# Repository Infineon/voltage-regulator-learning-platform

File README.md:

# Learning Platform for Switching Regulators

This platform is designed with the intention of providing an interactive educational opertunity to university students with diverse technical backgrounds on switching regulators (namely buck converters). The project aims to develop the students' skills on using basic microcontroller IO features as starters and then build upon those skills to use a gate driver to implement a buck converter and monitor its output and efficiency. Along the Buck converter design process, the students get to use the the on board's peripherals to understand the different properties of buck converters and how they could be optimized. 

## Project's History
The project was introduced as a bachelor thesis of **Lukas Wiegert**. (*version 1.0*). Continued and further developed by **Adrian Keil** (*Versions: 1.0 ,1.1 ,1.2*) and finalized by **Youssef Tarkhan** (*versions: 2.0, 2.1*). The latest update was done 2025 from **David Lopez** (*version: PCBv3*). The boards are used by the Technical University of Munich to teach the students and assess the quality and functionality of these boards and provide an open source curriculum.

# Latest Update PCBv3

The latest update included mainly following changes:
- Removing the 3.3V rail. Only two remaining power supply rails (12V for power part, 5V for digital logik and measurements).
- Fixed common error that current measurement opamps burn because of shorted ouputs (male pinheaders get easily shorted when probed)
- Additional output resistance as second safety measure

# Board Breakdown

**Brief summary**: As you can see from the block diagram, the board needs an input connection. (Bannana ports are provided at the bottom side of the board).  After the board makes sure that the polarity and the voltage are in check, the power is fed into the board's internal powersupply compartment. If the voltage level is below 10V then you will observe the undervoltage LED glowing in RED. The powerline feeding the whole board interfaces two optional possibilities for input current measurement. Power is then fed onto the power stage which consists of the components needed for the buck switching with a **VOut** output (*In older versions of the board there used to be additional banana ports for the **Vout** terminal and an additional ground banana port*.) Power is additionally fed into the arduino peripherals for basic microcontroller usage (LEDS, Switches, Buttons and Potentiometers). 

*Note that for every measurable quantity such as the input current for instance, there is a testpoint that could be attached onto an oscilloscope in order to have an easier experience when trying the measure this quantity*

# Microcontroller Pinouts
This platform is an arduino compatable shield. It is intended to be used in combination with the XMC1100 Bootkit
The labelling of the XMC1100 Bootkit pins is placed on the bottom layer's silk screen.

>An Arduino compatible shield is a hardware expansion board that is designed to be compatible with Arduino microcontroller boards. It is called a "shield" because it typically attaches on top of an Arduino board, extending its capabilities and providing additional functionalities

<center>

## XMC 1100 Bootkit Pins
| Pin   | Net                   | Type   | Description                                |
|-------|-----------------------|--------|--------------------------------------------|
| A0    | In_Curr_ADC           | Input  | Analog input for current measurement        |
| A1    | Inductor_Current_ADC  | Input  | Analog input for inductor current sensing   |
| A2    | UserPot1              | Input  | Analog input for user potentiometer 1       |
| A3    | Vin_Meas              | Input  | Analog input for voltage measurement        |
| A4    | Vout_Meas             | Input  | Analog input for output voltage measurement |
| A5    | NTC_ext               | Input  | Analog input for external NTC temperature    |
| D0    | NC                    | NC     | Not connected                              |
| D1    | NC                    | NC     | Not connected                              |
| D2    | UserBtn1              | Input  | Digital input for user button 1             |
| D3    | Cntrl1                | Output | Digital output for control signal 1         |
| D4    | Cntrl2                | Output | Digital output for control signal 2         |
| D5    | Cntrl3                | Output | Digital output for control signal 3         |
| D6    | Buck_Cntrl_Arduino    | Output | Digital output for Arduino buck control     |
| D7    | UserBtn2              | Input  | Digital input for user button 2             |
| D8    | Shutdown              | Input  | Digital input for shutdown signal           |
| D9    | User_LED1             | Output | Digital output for user LED 1               |
| D10   | User_LED2             | Output | Digital output for user LED 2               |
| D11   | User_LED3             | Output | Digital output for user LED 3               |
| D12   | UserSw                | Input  | Digital input for user switch               |
| D13   | User_LED4             | Output | Digital output for user LED 4               |

<br><br>
</center>

> **Note:** The following code snippet defines all the required arduino pins for using the platform, simply copy it to the beginning of your code (before the setup)

<br><br>
<center>

```cpp
// Define all Arduino pins
// Digital Out
#define USER_LED1     9
#define USER_LED2     10
#define USER_LED3     11
#define USER_LED4     13
#define BUCK_PIN      6

// Digital In
#define USER_BTN1     2
#define USER_BTN2     7
#define SHUTDOWN      8
#define USER_SW       12

// Analog In
#define IN_CURR       A0
#define INDUCTOR_CURR A1
#define USER_POTI     A2

#define VIN_MEAS      A3
#define VOUT_MEAS     A4
#define NTC           A5

```

</center>
<br>
<br>
Also add the following pin setup lines into your setup loop 

<center>

```cpp
  pinMode(BUCK_PIN, OUTPUT);
  pinMode(USER_LED1, OUTPUT);
  pinMode(USER_LED2, OUTPUT);
  pinMode(USER_LED3, OUTPUT);
  pinMode(USER_LED4, OUTPUT);
  pinMode(USER_BTN1, INPUT);
  pinMode(USER_BTN2, INPUT);
  pinMode(USER_SW, INPUT);
  pinMode(SHUTDOWN,INPUT);
  pinMode(USER_POTI,INPUT);
  pinMode(INDUCTOR_CURR,INPUT);
  pinMode(IN_CURR,INPUT);

```

</center>
<br>
<br>

> **Note:** In order to use both user buttons you'll have to unsolder the resistor at Pin 1.4 (check out the diagram below)

<p align="center">
  
</p>

# Power Input
The board is equipped with a variety of safety measures to ensure that it not only has a long life, but also ensure that students get to have a higher level of freedom with it. The board is to be powered with a DC power supply through banana plugs. 

- First stage of the power input is going through the reverse polarity protection circuit, following by over voltage detection circuit. ( In case of an overvoltage detection, power is cut from the main circuit through a MOSFET) Note that the board supports up to 30V but has a recommended to be used in the 15V input range
- Voltage is then delivered to the board compartments : Powersupply, Safety Comparator, Powerstage stage & Miscellaneous  

# Power Supply
The Optimum input Voltage for the board input is around **15V**. In case the voltage goes over 19V the board goes into a hysterisis where it only gets back in operation when the voltage level goes below ****. Feel free to check the simulation files if you want to get a deeper insight into how the hysterisis works on a circuit design level. (You will have to install the spice model files for the ATL431, [click here](https://www.youtube.com/watch?v=EwAxUvS5z-0) for a guide on how to do that)
Along with the input being fed into the board, the board additionally has 3 additional power components which are:
<center>

 **12V LDO**: 
<p align="center">
  
</p>
	- Gate driver IC
	- Input Internal Current Sense Amplifier
	- Safety Latch 
	- Safety Circuit Comparator
	- Safety LEDs

**5V Buck**: 
<p align="center">
  
</p>
	- 3V3 LDO
	- Arduino Compatable MCU 
	- Safety Circuitry Voltage Threshhold (*Under-Voltage Detection*)
  
**3V3 LDO**:
<p align="center">
  
</p>
	- Output Internal Current Sense Amplifier
	- ADC Compensation for MCU Input
	- Safety Comparator Circuit
</center>		

<br><br>

# Safety
The safety compartment of the board is comprised mainly of a comparator and a safety latch, where when the safety comparator detects a flag, this flag is saved on the latch. (To reset the latch all you'll have to do is press the latch reset button)

For example if the undervoltage flag is raised (Input voltage goes below 10V), the undervoltage flag will be raised and the corresponding LED will turn on. Aslong as the latch has not been reset, even if the input voltage goes above 10V, the LED will stay on and the shutdown signal will keep getting sent to the microcontroller and the power components. 

**Flags**

When safety flags are triggered, a **shutdown** signal is generated and the corresponding flag's LED is lit. The **shutdown** signal is delivered to the microcontroller and the power stage components. The powerstage is disabled as long as the shutdown signal is being delivered to its components.  

- **Overcurrent**
  - The output current from the powerstage is measured over a shuntresistor and a current sense amplifier. The output signal is then fed into a the safety comparator, which is compared to a constant reference voltage. (This reference voltage is equal to the corresponding output of the amplifier when the output current is around **2.8A**). 

- **Undervoltage**
  - the input voltage is fed through the two equal value resistors R510 and R511 and the signal is halfed (voltage divider Law), and is then fed into the comparator. As reference the 5V Buck output is fed into the other input of the comparator. If the input voltage goes below 10V , then half of that signal will be lower than 5V and so the undervoltage flag would be triggered.

- **Overtemperature (External)**
  - An NTC is connected on the external resistor board. (Negative Thermal cooefficient resistor; pretty much a fancy word for a resistor, who's resistance value changes when its temperature changes). The NTC's signal is connected to an input of the safety comparator with a reference signal connected to the other input.
    
- **Overtemperature (Internal)**
  - Similar to external overtemperature detection, however the NTC is onboard and there is a variable resisotr on board to calibrate the onboard overtemperature limit of the board. 

- **Safety Flag LEDs**
  - you can find the safety LEDs are placed on the top right corner of the PCB

<br><br>
## Miscellaneous
The board is equipped with:
- 1 User programmable potentiometer
  
- 2 User programmable buttons
  
- 4 User programmable LEDs

- 1 User programmable Switch

<br>

##  Buck Operation
The buck operation takes place over a gate driver; what happens: is that the gate driver takes in pulse width modulated signals from the microcontroller (**XMC 1100 Bootkit**) or an external controller through the **PWM** pin on the external control pin header.  The users have to modify the **BUCK CNTRL** switch to adapt the circuitry to whether or not the control signal would be coming from the external control pin header or through the onboard controller pins. The students get to change the frequency and duty cycle of the signal in order to achieve their desired output voltage. 

There are also some jumpers on board that could adjust the output circuity of the buck operation.
Jumpers are available for: 
- Connecting three 10 uF Capacitors 
- Connecting a 220uF capacitor
- Connecting a 15uH inductor

## External Control

Aside from using the board as a shield, it could also just be connected to an external controller circuit.

As shown in the diagram above, using jumper cables, the user externally has access to: 

- Input voltage to through the Banana cables
- 12V Output of the LDO
- 5V Output of the Buck Controller
- 3.3V Output of the LDO
- Input Current Sensor Reading
- Output Current Sensor Reading
- Output Voltage 
- Output Voltage (Calibrated to 0 to 5V)
- External Buck Control
- User Button 1 Input
- User Button 2 Input
- User Switch Input
- User LEDs (1 to 3)
- User Potentiometer 1 Input

### NTC Calibration
- For making sure that the temperature on board is in check, negative thermal coefficient resistors are chosen . The onboard maximum temperature could easily be calibrated by adjusting a potentiometer for temperature limitation between (50°C and 90°C)

## Current Measurement
The main method of current measurement is the combination of a shunt resistor and a current sense amplifier. This setup is repeated in the input and output current measurement system. The operation relies on a voltage drop accross the shunt resistor proportional to the current flowing through it. This voltage drop is amplified by the current sense amplifier into a new voltage value. This voltage value is read by the micro-controller's ADC and it's used to subsequently calculate the value of the current.

the main component (TSC2010IST) in the diagram above is a current sense amplifier. This current sense amplifier is connected over a shunt resistor (pins: 1 & 8). The output of this amplifier is proportional to the amount of current going through the shunt resistor. 

<br>

# Testpoints

The board is equiped with test points to make it easier for students to observe different quantities using an oscilloscope.

<center>

All black testpoints are Ground testpoints

Red testpoints are labelled with their corresponding measurement quantity. 

</center>
<br>

# Simulation Files
To provide a rich experience to students, the simulation files for most of the building blocks of the learning platform are provided. These simulations are accessable on LTSPICE, which is an open source freeware, that is very popular in the industry.  

You can find these simulations under the Directory /Simulations.
<br>

# Future Strategy 
This project is not yet fully disclosed, and it will remain under  development so feel free to reach out to youssef.tarkhan@infineon.com for any inquiries or suggestions anytime.

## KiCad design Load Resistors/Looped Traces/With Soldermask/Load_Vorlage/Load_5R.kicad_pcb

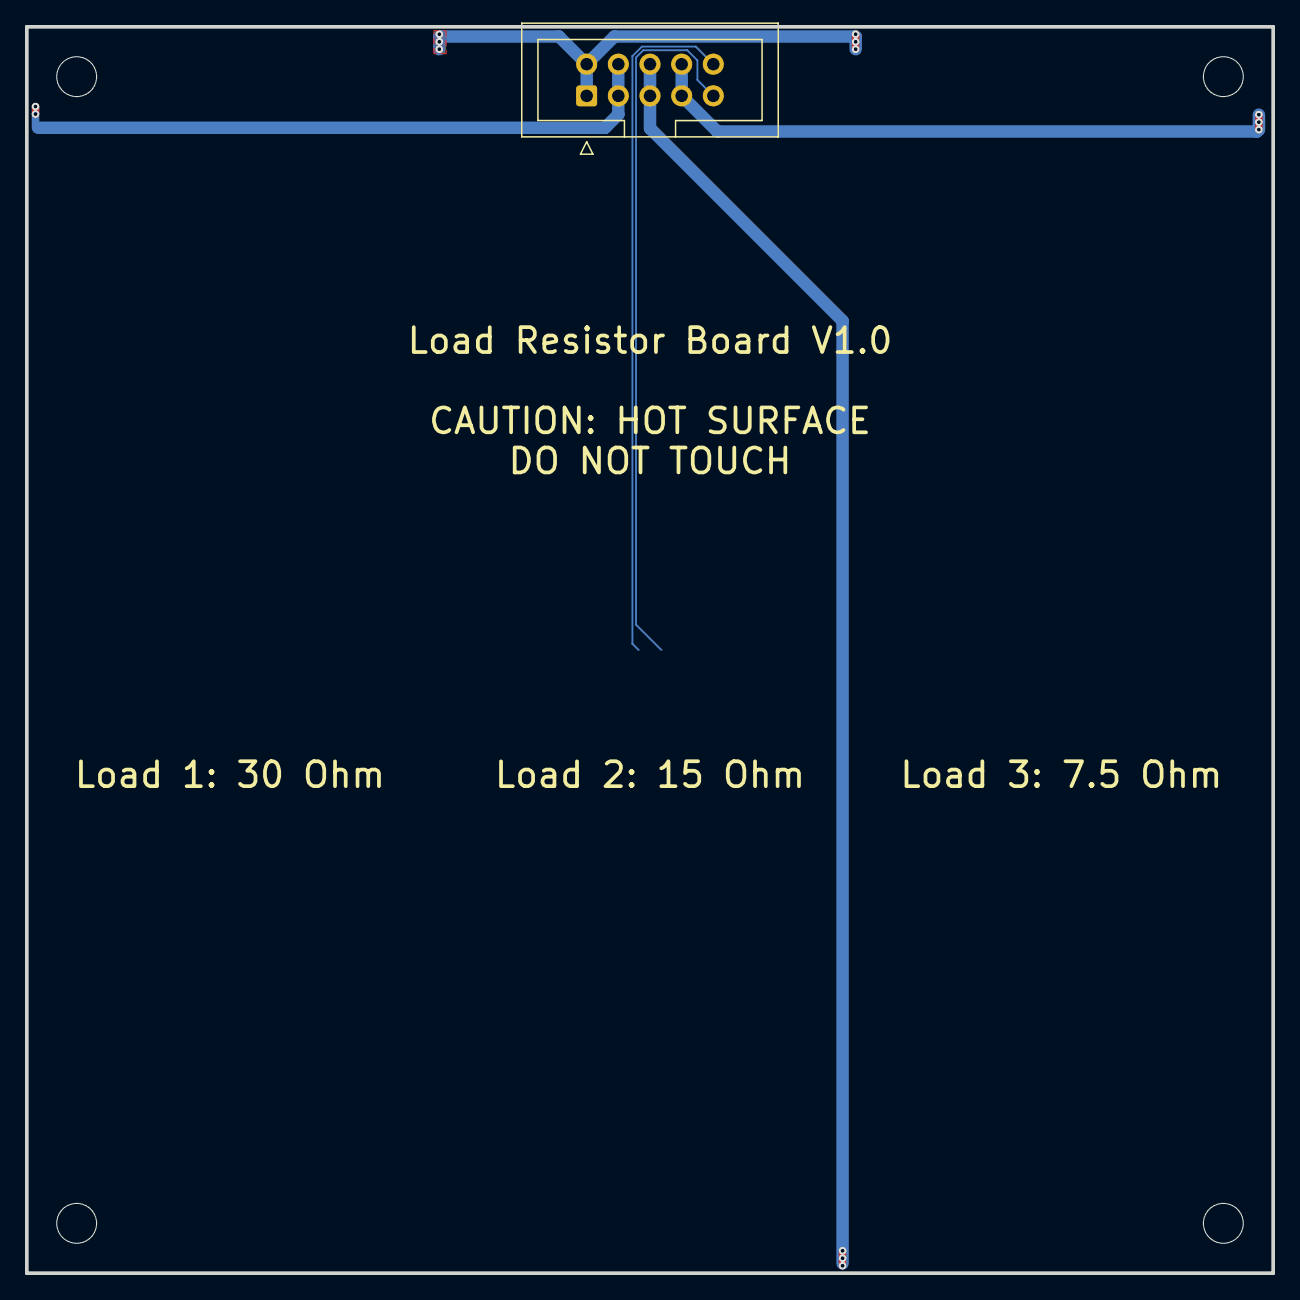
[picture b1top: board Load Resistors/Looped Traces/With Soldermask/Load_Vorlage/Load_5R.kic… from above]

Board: 2 copper layers, 100.0 x 100.0 mm, 6 parts (1 on the bottom side), 3 nets.

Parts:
H1, H2, H3, H4: MountingHole; MountingHole_3.2mm_M3
J1: Conn_02x05_Odd_Even; IDC-Header_2x05_P2.54mm_Vertical
TH1: Thermistor_NTC; R_0603_1608Metric_Pad0.98x0.95mm_HandSolder

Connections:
/Loads: J1.1, J1.2, J1.3, J1.4, J1.5, J1.6, J1.7, J1.8
/NTC_ext: J1.9, TH1.2
GND: J1.10, TH1.1

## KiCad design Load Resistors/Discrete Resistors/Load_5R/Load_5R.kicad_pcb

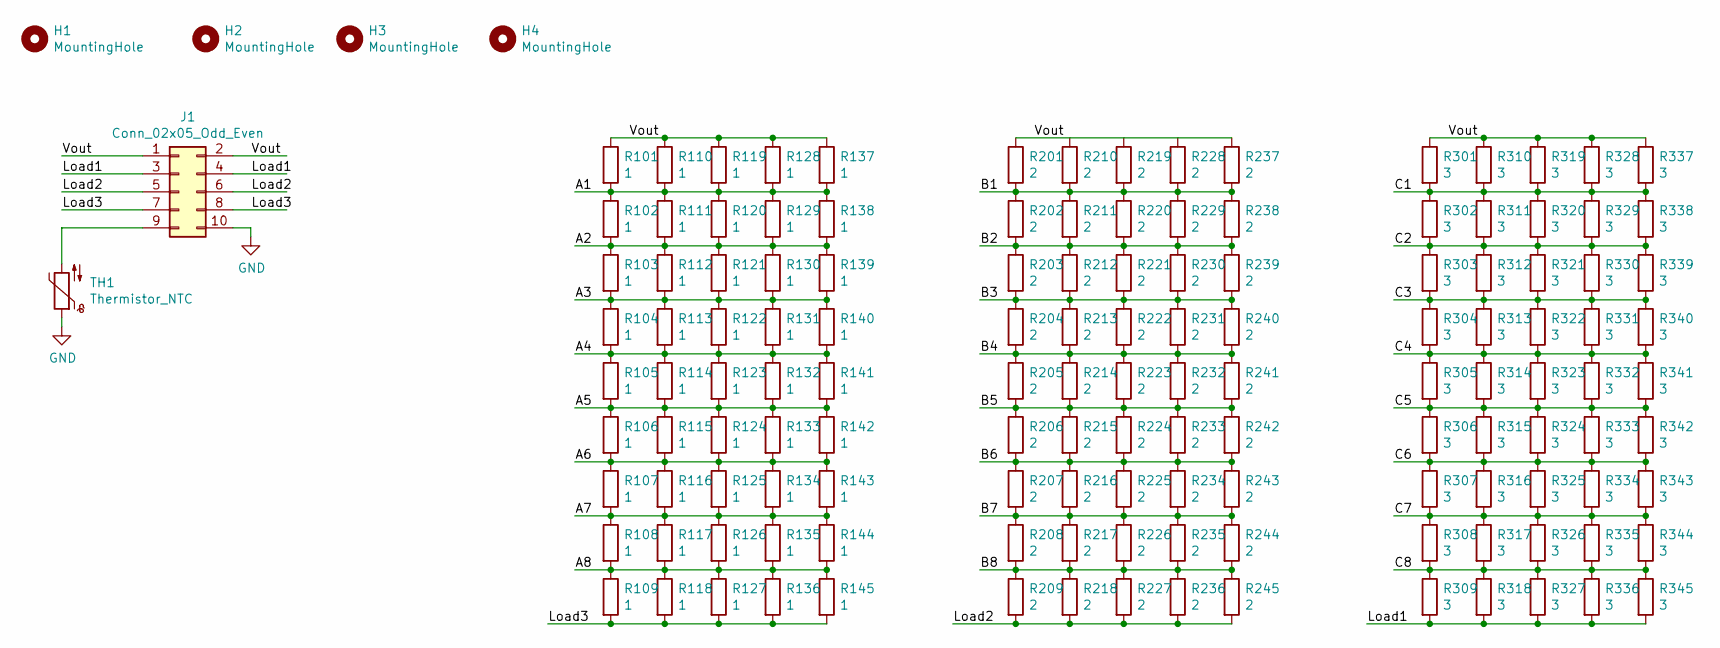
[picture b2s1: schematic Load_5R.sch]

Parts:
H1, H2, H3, H4: MountingHole; MountingHole_3.2mm_M3
J1: Conn_02x05_Odd_Even; IDC-Header_2x05_P2.54mm_Vertical
R101, R102, R103, R104, R105, R106, R107, R108, R109, R110, R111, R112, R113, R114, R115, R116, R117, R118, R119, R120, R121, R122, R123, R124, R125, R126, R127, R128, R129, R130, R131, R132, R133, R134, R135, R136, R137, R138, R139, R140, R141, R142, R143, R144, R145: 1; R_2512_6332Metric; LCSCPart C10000
R201, R202, R203, R204, R205, R206, R207, R208, R209, R210, R211, R212, R213, R214, R215, R216, R217, R218, R219, R220, R221, R222, R223, R224, R225, R226, R227, R228, R229, R230, R231, R232, R233, R234, R235, R236, R237, R238, R239, R240, R241, R242, R243, R244, R245: 2; R_2512_6332Metric; LCSCPart C20000
R301, R302, R303, R304, R305, R306, R307, R308, R309, R310, R311, R312, R313, R314, R315, R316, R317, R318, R319, R320, R321, R322, R323, R324, R325, R326, R327, R328, R329, R330, R331, R332, R333, R334, R335, R336, R337, R338, R339, R340, R341, R342, R343, R344, R345: 3; R_2512_6332Metric; LCSCPart C30000
TH1: Thermistor_NTC; R_0603_1608Metric_Pad0.98x0.95mm_HandSolder; LCSCPart C92367

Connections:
/A1: R101.2, R102.1, R110.2, R111.1, R119.2, R120.1, R128.2, R129.1, R137.2, R138.1
/A2: R102.2, R103.1, R111.2, R112.1, R120.2, R121.1, R129.2, R130.1, R138.2, R139.1
/A3: R103.2, R104.1, R112.2, R113.1, R121.2, R122.1, R130.2, R131.1, R139.2, R140.1
/A4: R104.2, R105.1, R113.2, R114.1, R122.2, R123.1, R131.2, R132.1, R140.2, R141.1
/A5: R105.2, R106.1, R114.2, R115.1, R123.2, R124.1, R132.2, R133.1, R141.2, R142.1
/A6: R106.2, R107.1, R115.2, R116.1, R124.2, R125.1, R133.2, R134.1, R142.2, R143.1
/A7: R107.2, R108.1, R116.2, R117.1, R125.2, R126.1, R134.2, R135.1, R143.2, R144.1
/A8: R108.2, R109.1, R117.2, R118.1, R126.2, R127.1, R135.2, R136.1, R144.2, R145.1
/B1: R201.2, R202.1, R210.2, R211.1, R219.2, R220.1, R228.2, R229.1, R237.2, R238.1
/B2: R202.2, R203.1, R211.2, R212.1, R220.2, R221.1, R229.2, R230.1, R238.2, R239.1
/B3: R203.2, R204.1, R212.2, R213.1, R221.2, R222.1, R230.2, R231.1, R239.2, R240.1
/B4: R204.2, R205.1, R213.2, R214.1, R222.2, R223.1, R231.2, R232.1, R240.2, R241.1
/B5: R205.2, R206.1, R214.2, R215.1, R223.2, R224.1, R232.2, R233.1, R241.2, R242.1
/B6: R206.2, R207.1, R215.2, R216.1, R224.2, R225.1, R233.2, R234.1, R242.2, R243.1
/B7: R207.2, R208.1, R216.2, R217.1, R225.2, R226.1, R234.2, R235.1, R243.2, R244.1
/B8: R208.2, R209.1, R217.2, R218.1, R226.2, R227.1, R235.2, R236.1, R244.2, R245.1
/C1: R301.2, R302.1, R310.2, R311.1, R319.2, R320.1, R328.2, R329.1, R337.2, R338.1
/C2: R302.2, R303.1, R311.2, R312.1, R320.2, R321.1, R329.2, R330.1, R338.2, R339.1
/C3: R303.2, R304.1, R312.2, R313.1, R321.2, R322.1, R330.2, R331.1, R339.2, R340.1
/C4: R304.2, R305.1, R313.2, R314.1, R322.2, R323.1, R331.2, R332.1, R340.2, R341.1
/C5: R305.2, R306.1, R314.2, R315.1, R323.2, R324.1, R332.2, R333.1, R341.2, R342.1
/C6: R306.2, R307.1, R315.2, R316.1, R324.2, R325.1, R333.2, R334.1, R342.2, R343.1
/C7: R307.2, R308.1, R316.2, R317.1, R325.2, R326.1, R334.2, R335.1, R343.2, R344.1
/C8: R308.2, R309.1, R317.2, R318.1, R326.2, R327.1, R335.2, R336.1, R344.2, R345.1
/Load1: J1.3, J1.4, R309.2, R318.2, R327.2, R336.2, R345.2
/Load2: J1.5, J1.6, R209.2, R218.2, R227.2, R236.2, R245.2
/Load3: J1.7, J1.8, R109.2, R118.2, R127.2, R136.2, R145.2
/Vout: J1.1, J1.2, R101.1, R110.1, R119.1, R128.1, R137.1, R201.1, R237.1, R301.1, R310.1, R319.1, R328.1, R337.1
GND: J1.10, TH1.1
unnamed: J1.9, TH1.2

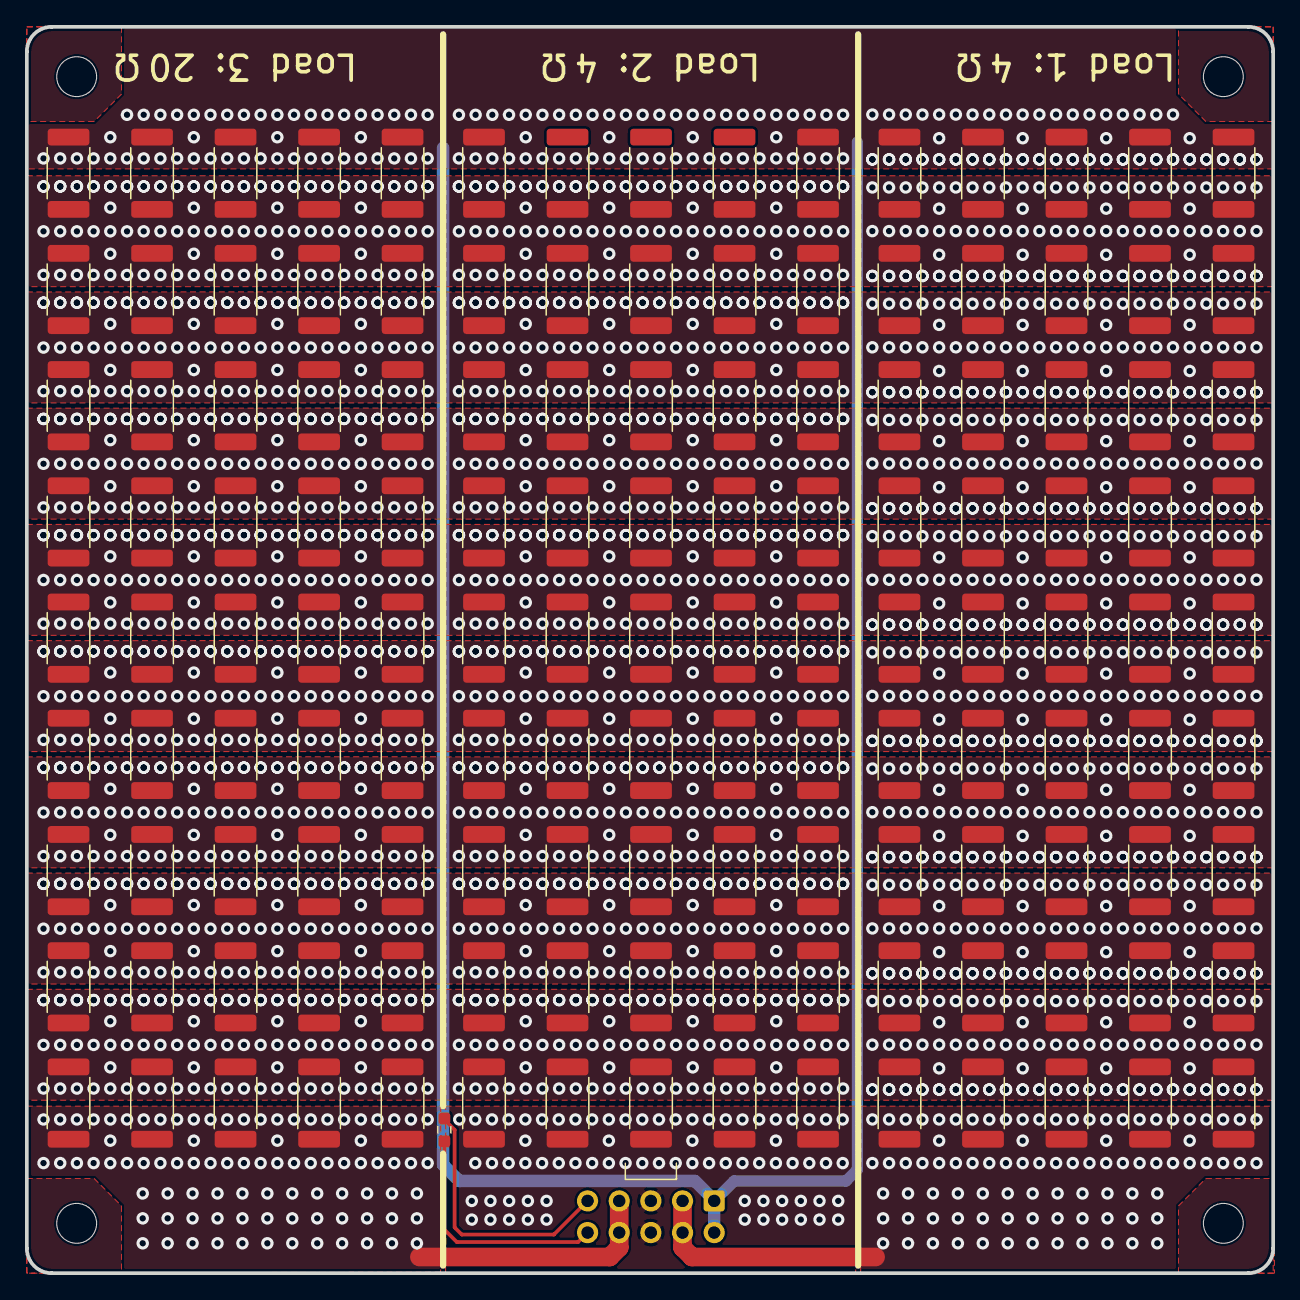
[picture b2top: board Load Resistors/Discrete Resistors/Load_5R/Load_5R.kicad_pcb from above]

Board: 2 copper layers, 100.0 x 100.0 mm, 141 parts (0 on the bottom side), 30 nets.

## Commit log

2022-12-13 primary import
2022-12-13 updated markdown file
2023-01-10 Changed to ATL431BQDBZR
2023-01-12 basic MD Update
2023-05-11 version 2.2 stable
2023-05-12 stabil 2.2
2023-05-12 output management
2023-05-21 intermediate MD
